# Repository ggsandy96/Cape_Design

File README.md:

# Cape_Design
The Cape for beagle bone has the options for ADC to BBB till 24V and an power controller circuit, with reverse polarity protection and over voltage protection. Apart from these, there was an interrupt generator, which generates an interrupt when the power goes off and BBB shifts to battery power

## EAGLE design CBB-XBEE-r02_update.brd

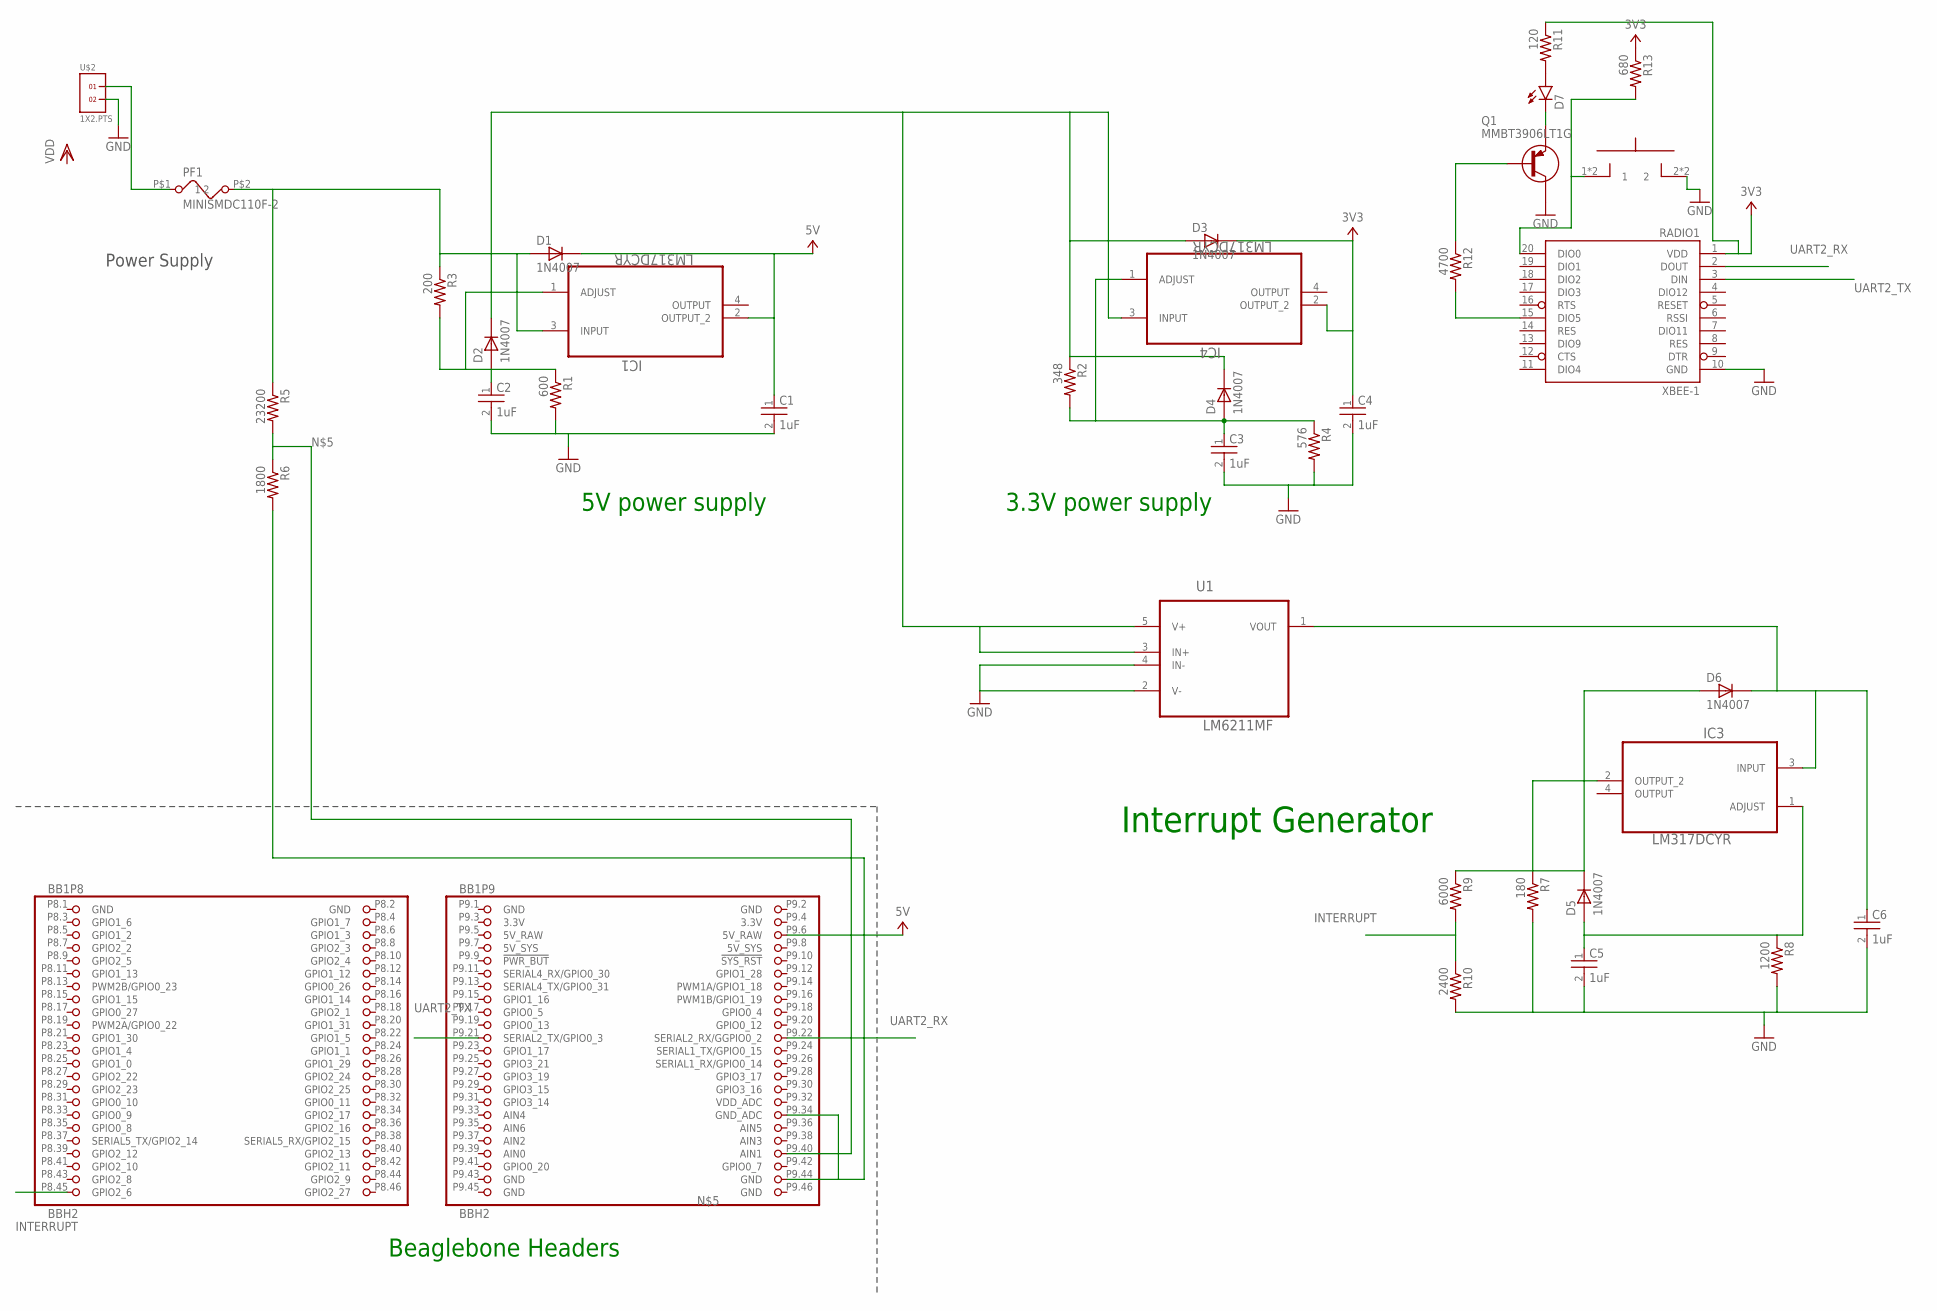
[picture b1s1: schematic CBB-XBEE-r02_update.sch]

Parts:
BB1: BBH2; BB_CAPE_TOP
C1, C2, C3, C4, C5, C6: 1uF; CAPC2012X135N
D1, D2, D3, D4, D5, D6: 1N4007; DIOAD1070W78L465D235P
D7: LED3MM
IC1, IC3, IC4: LM317DCYR; SOT230P700X180-4N
PF1: MINISMDC110F-2; MINISMDC110
Q1: MMBT3906LT1G; SOT23
R1: 600; 0603-RES
R2: 348; 0603-RES
R3: 200; 0603-RES
R4: 576; 0603-RES
R5: 23200; 0603-RES
R6: 1800; 0603-RES
R7: 180; 0603-RES
R8: 1200; 0603-RES
R9: 6000; 0603-RES
R10: 2400; 0603-RES
R11: 120; 0603-RES
R12: 4700; 0603-RES
R13: 680; 0603-RES
RADIO1: XBEE-1; XBEE
U1: LM6211MF; SOT95P284X122-5N
U$1: SPST-NOKS-01Q-01; KS-01Q-01
U$2: 1X2.PTS; PTS.FIXED

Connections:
3.3V: BB1.P9.3 (3.3V), BB1.P9.4 (3.3V)
3V3: C4.1 (A), D3.C, IC4.2 (OUTPUT_2), R11.1, R13.1, RADIO1.1 (VDD)
5V: BB1.P9.6 (5V_RAW), C1.1 (A), D1.C, IC1.2 (OUTPUT_2)
5V_RAW: BB1.P9.5 (5V_RAW)
5V_SYS: BB1.P9.7 (5V_SYS), BB1.P9.8 (5V_SYS)
GND: BB1.P8.1 (GND), BB1.P8.2 (GND), BB1.P9.1 (GND), BB1.P9.2 (GND), C1.2 (C), C2.2 (C), C3.2 (C), C4.2 (C), C5.2 (C), C6.2 (C), Q1.3 (C), R1.2, R4.2, R7.2, R8.2, R10.2, RADIO1.10 (GND), U1.2 (V-), U1.4 (IN-), U$1.2, U$1.4 (2), U$2.2
INTERRUPT: BB1.P8.45 (GPIO2_6), R9.2, R10.1
unnamed: C3.1 (A), D4.A, IC4.1 (ADJUST), R2.2, R4.1
unnamed: D5.C, D6.A, IC3.2 (OUTPUT_2), R7.1, R9.1
unnamed: C2.1 (A), D2.A, IC1.1 (ADJUST), R1.1, R3.2
unnamed: BB1.P9.40 (AIN1), R5.2, R6.1
unnamed: R12.2, RADIO1.15 (DIO5)
unnamed: D1.A, D2.C, D3.A, D4.C, IC1.3 (INPUT), IC4.3 (INPUT), PF1.P$2 (2), R2.1, R3.1, R5.1, U1.3 (IN+), U1.5 (V+)
unnamed: Q1.1 (B), R12.1
unnamed: C5.1 (A), D5.A, IC3.1 (ADJUST), R8.1
unnamed: C6.1 (A), D6.C, IC3.3 (INPUT), U1.1 (VOUT)
unnamed: R13.2, RADIO1.20 (DIO0), U$1.1, U$1.3 (1)
unnamed: D7.A, R11.2
unnamed: D7.K (C), Q1.2 (E)
unnamed: PF1.P$1 (1), U$2.1
unnamed: BB1.P9.34 (GND_ADC), BB1.P9.44 (GND), R6.2
UART2_RX: BB1.P9.22 (SERIAL2_RX/GGPIO0_2), RADIO1.2 (DOUT)
UART2_TX: BB1.P9.21 (SERIAL2_TX/GPIO0_3), RADIO1.3 (DIN)

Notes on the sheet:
Power Supply
Beaglebone Headers
5V power supply
3.3V power supply
Interrupt Generator

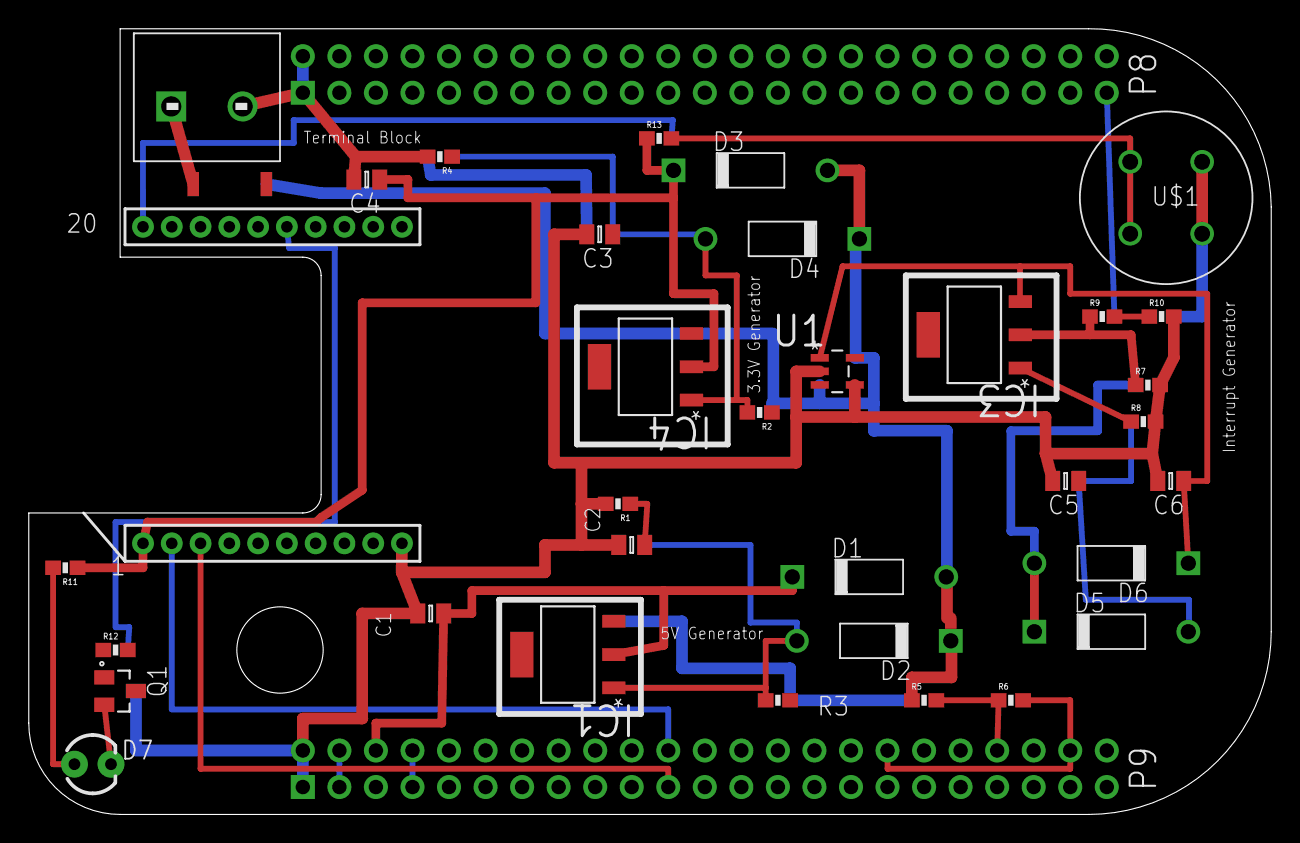
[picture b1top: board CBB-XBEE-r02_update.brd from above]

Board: 2 copper layers, 86.4 x 54.6 mm, 36 parts (1 on the bottom side), 22 nets.

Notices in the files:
parts and their libraries:
sparkres: Licensing: Creative Commons ShareAlike 4.0 International - https://creativecommons.org/licenses/by-sa/4.0
